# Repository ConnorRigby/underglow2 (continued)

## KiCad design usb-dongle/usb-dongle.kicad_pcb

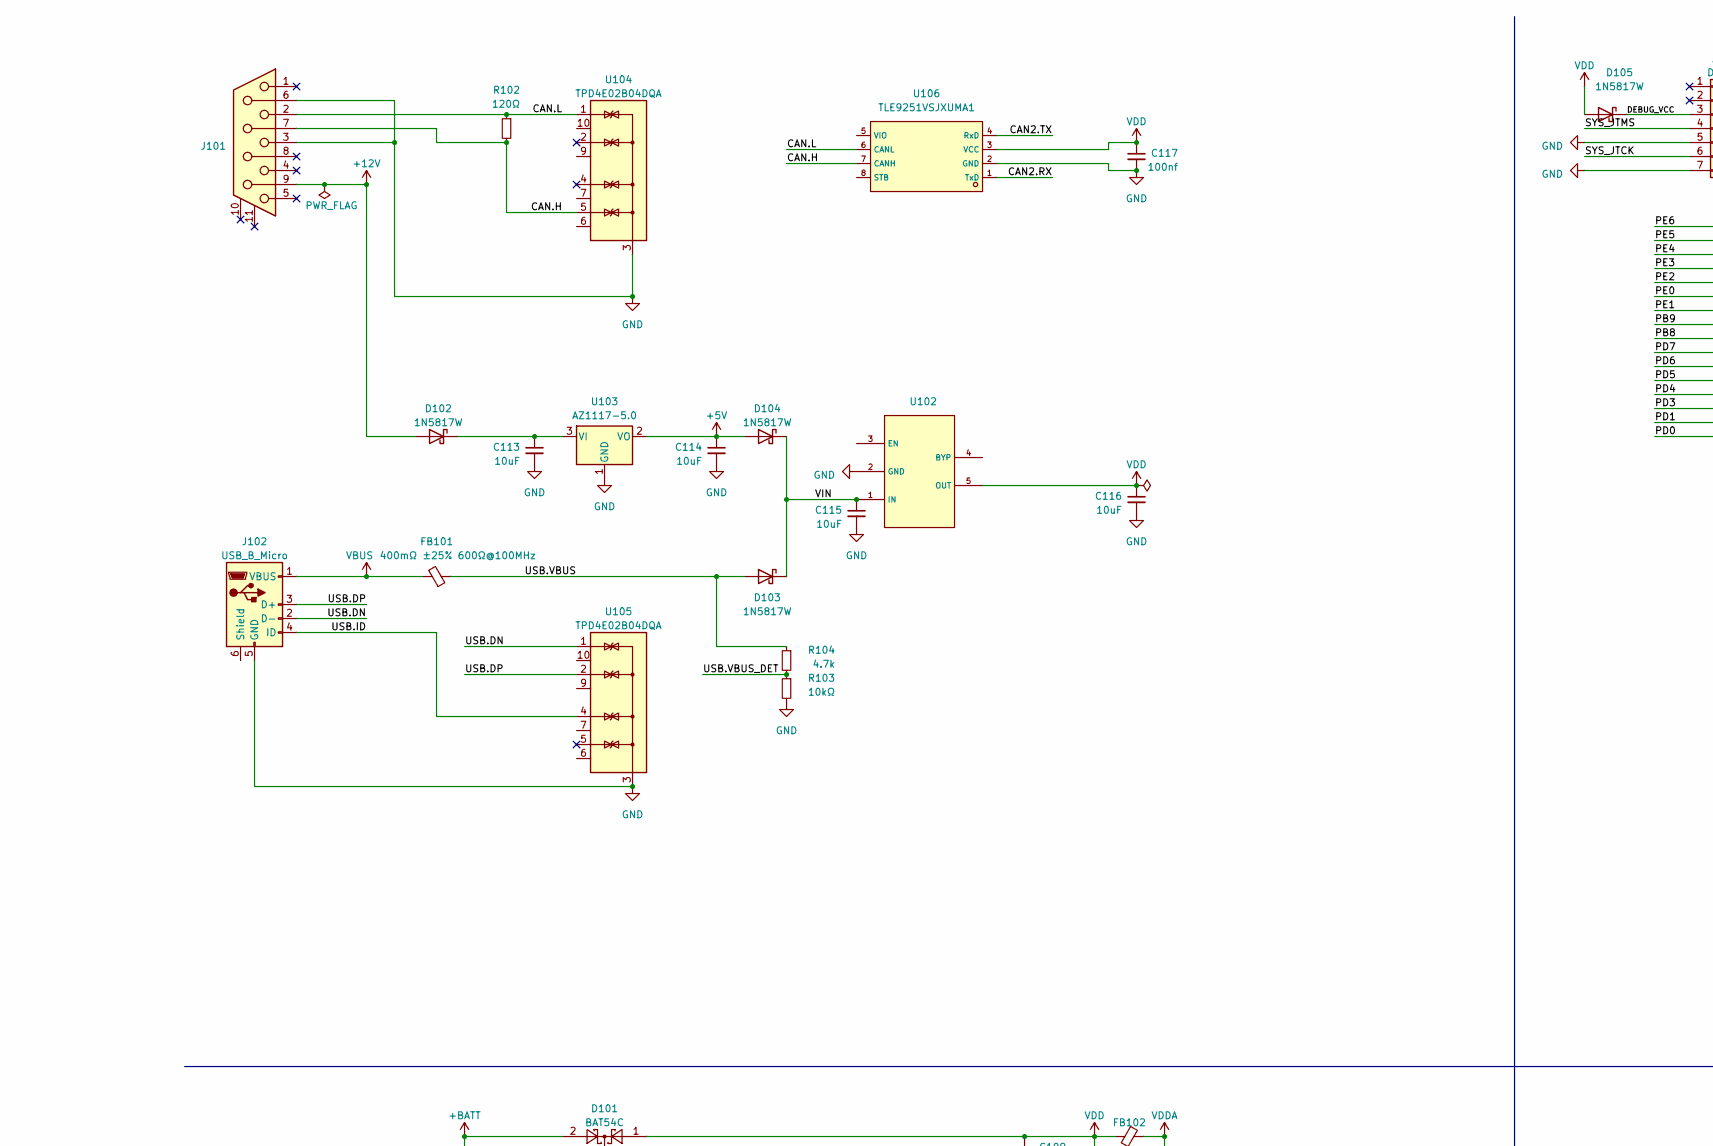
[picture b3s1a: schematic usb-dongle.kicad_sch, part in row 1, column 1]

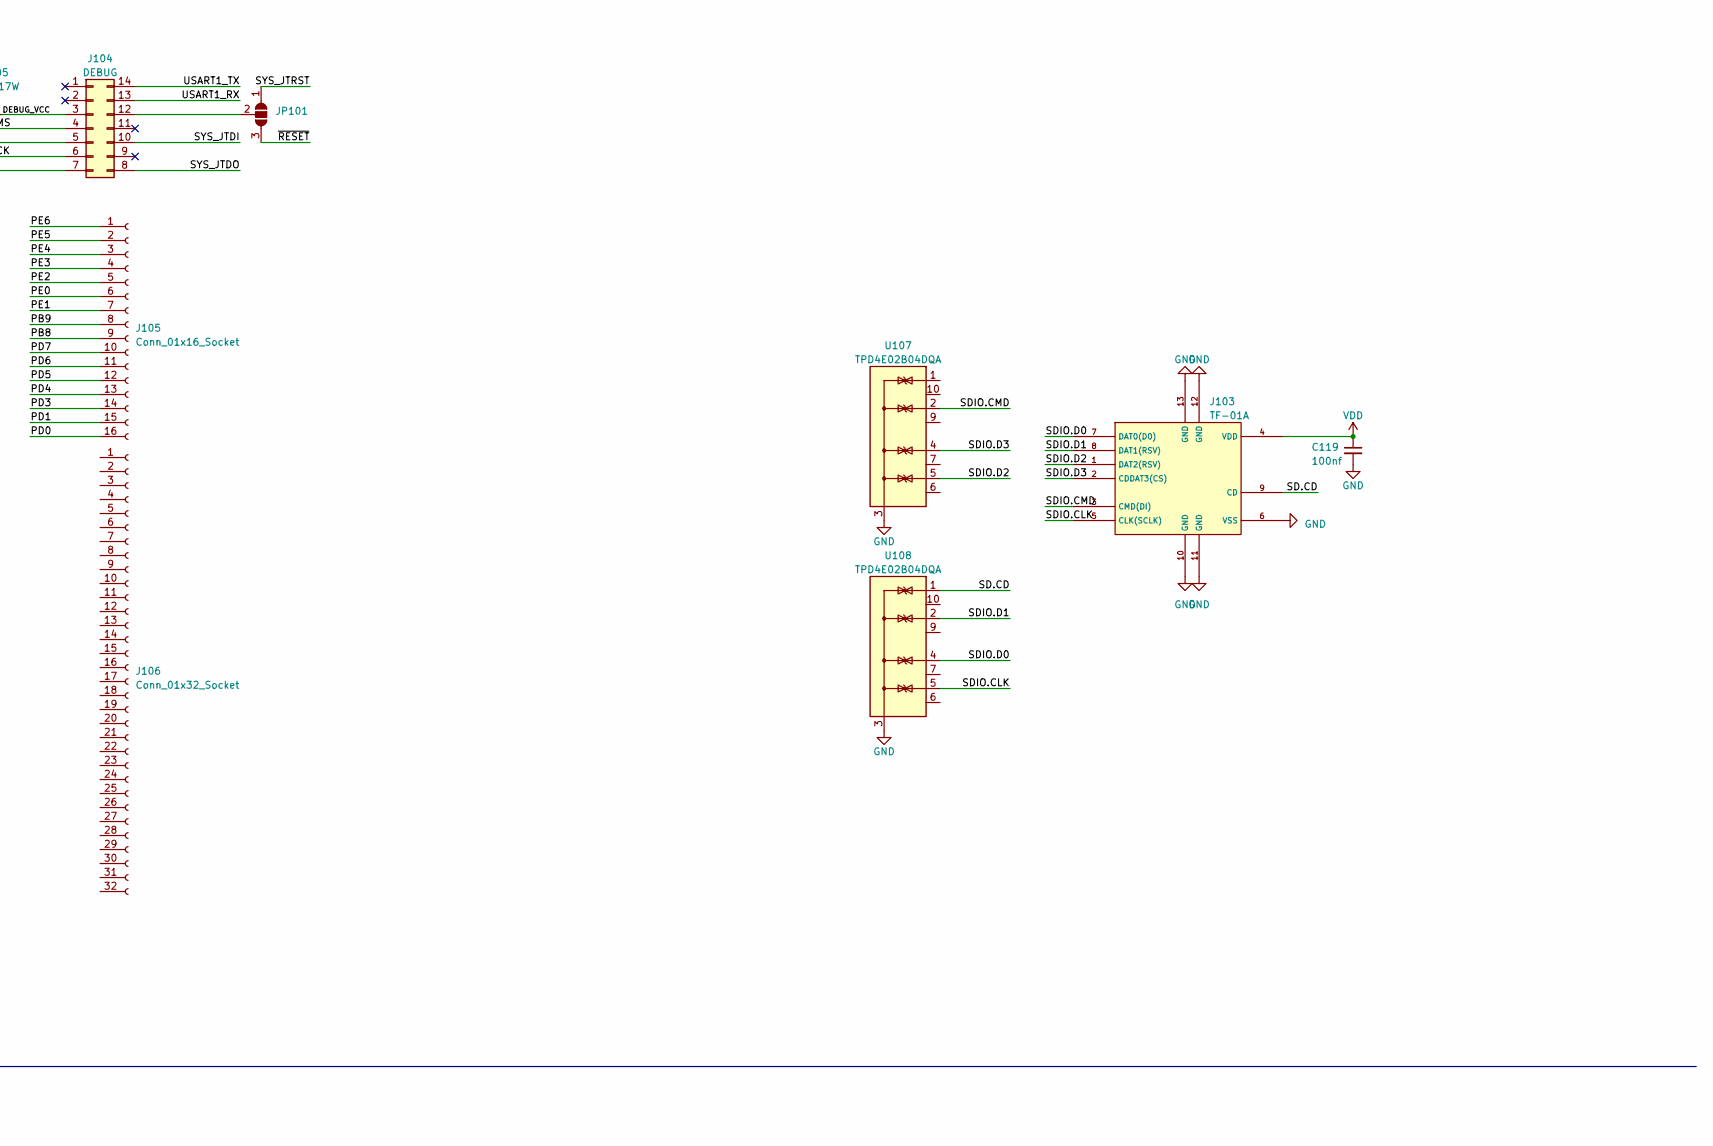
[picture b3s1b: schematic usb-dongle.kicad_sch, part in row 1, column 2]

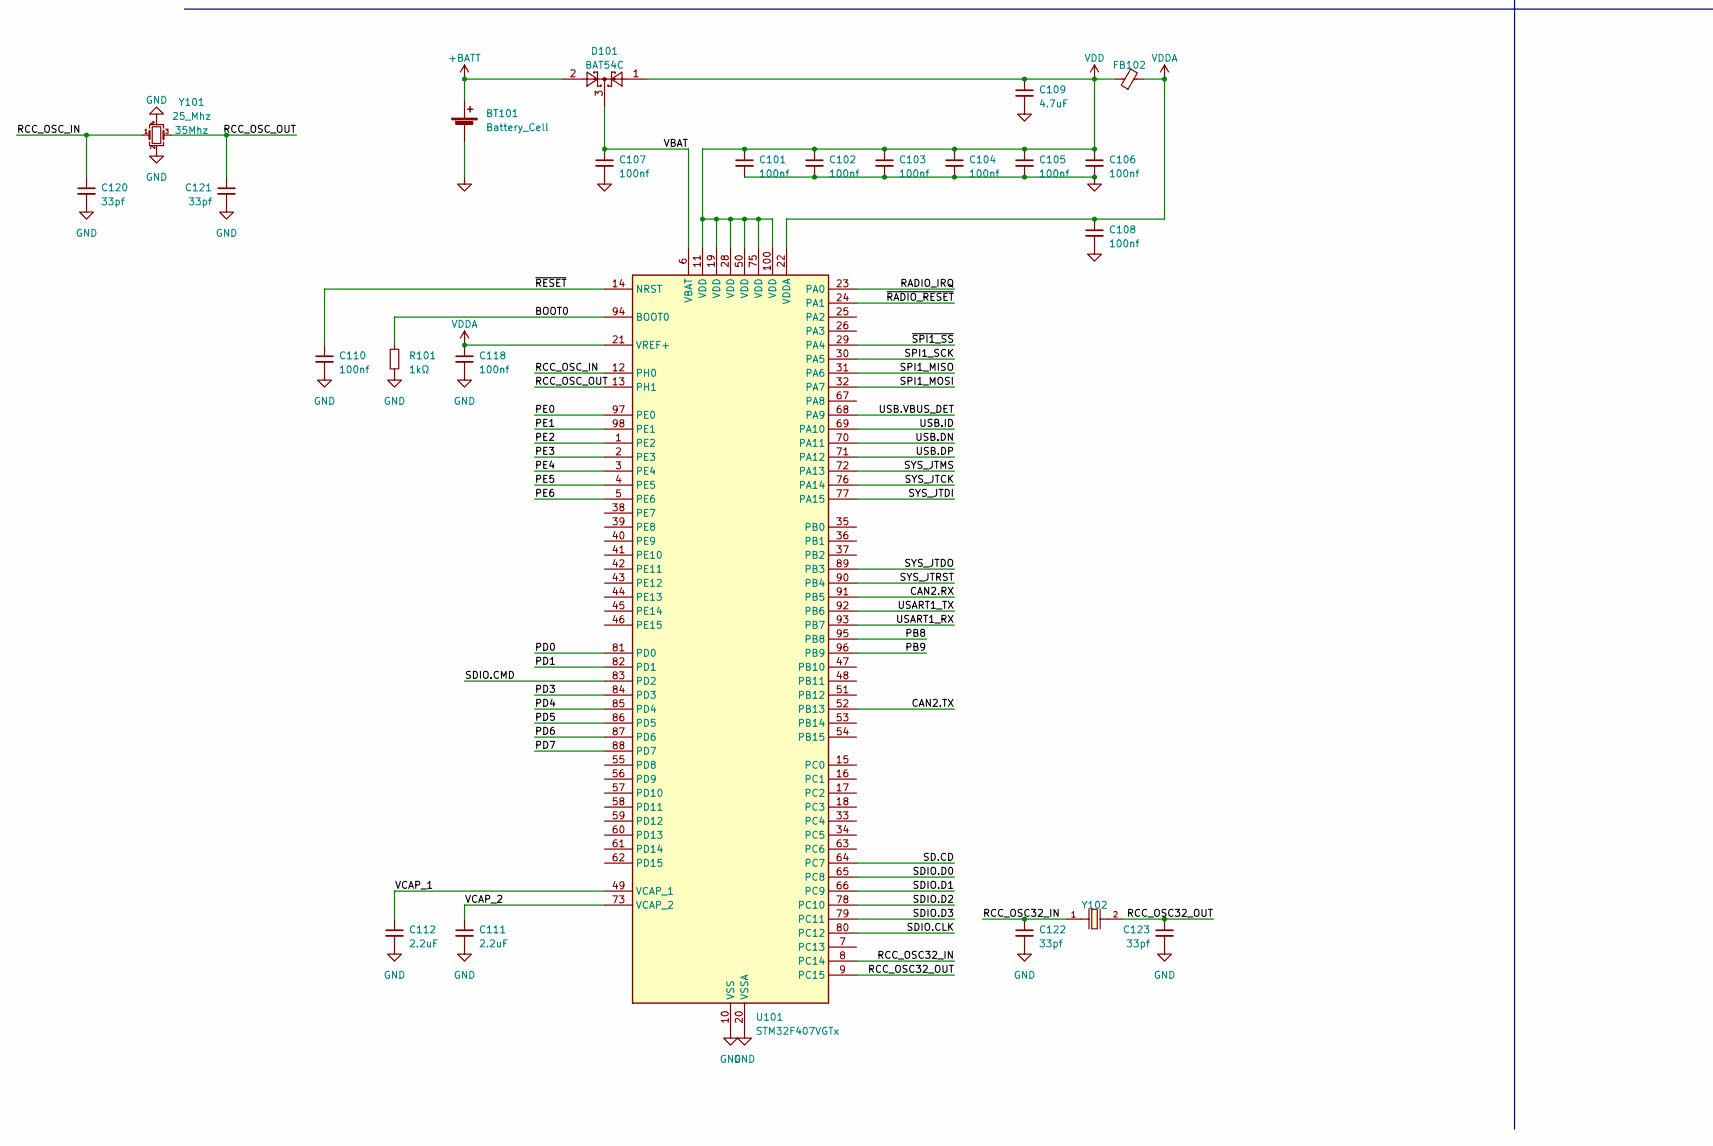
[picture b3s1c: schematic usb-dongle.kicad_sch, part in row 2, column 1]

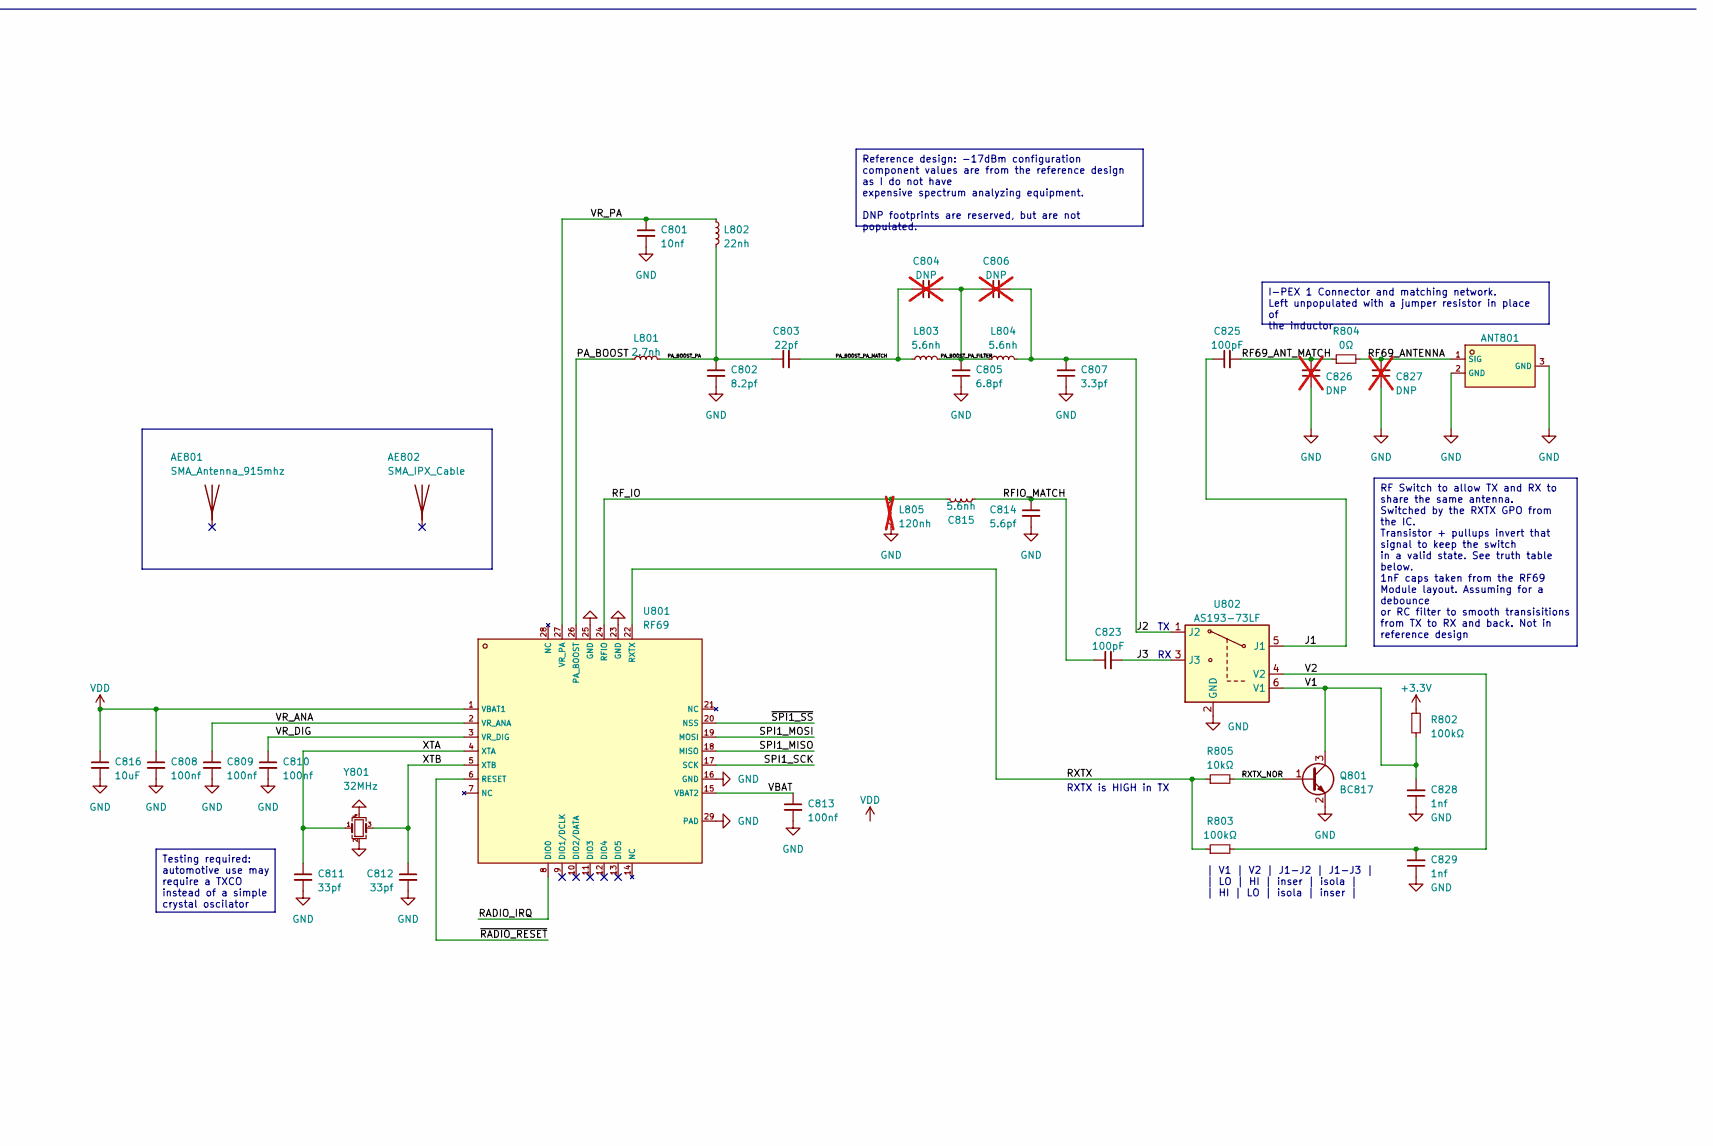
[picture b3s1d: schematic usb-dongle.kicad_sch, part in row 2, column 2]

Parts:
AE801: SMA_Antenna_915mhz; SMA_Antenna_Vertical; MPN TX915-JK-11; LCSC C468327
AE802: SMA_IPX_Cable; SMA_Connector; MPN BWIPX1-SMA-1.13L100; LCSC C784403
ANT801: BWIPX-1-001E; IPEX-SMD_BWIPX-1-001E; MPN BWIPX-1-001E; LCSC C496552
BT101: Battery_Cell; BAT-TH_CR2032-BS-6-1
C101, C102, C103, C104, C105, C106, C107, C108, C110, C117, C118, C119, C808, C809, C810, C813: C_0402_100nf_X7R; C_0402_1005Metric; Voltage 50V; MPN 0402B104K500NT; LCSC C110251
C109: C_0805_4u7_X5R; C_0805_2012Metric; Voltage 6.3; Tolerance 20%; MPN CC0805MKX5R5BB475; LCSC C577033
C111, C112: C_0402_2u2_X75R; C_0402_1005Metric; Voltage 25V; Tolerance 10%; MPN GRM155R61E225KE11D; LCSC C385032
C113, C114, C115, C116, C816: C_0805_10u_X5R; C_0805_2012Metric; Voltage 35V; Tolerance 10%; MPN GRM21BR6YA106KE43L; LCSC C162422
C120, C121, C122, C123, C811, C812: C_0402_33p_C0G; C_0402_1005Metric; Voltage 50V; Tolerance 2%; LCSC C76905
C801: C_0402_10n_C0G; C_0402_1005Metric; Voltage 35V; Tolerance ±5%; MPN GRM1555CYA103JE01D; LCSC C1518210
C802: C_0402_8p2_C0G; C_0402_1005Metric; Voltage 50V; Tolerance 2%; MPN GJM1555C1H8R2CB01D; LCSC C88898
C803: C_0402_22p_C0G; C_0402_1005Metric; Voltage 50V; Tolerance 2%; MPN GJM1555C1H220GB01D; LCSC C161315
C804, C806, C826, C827: C_0402_DNP; C_0402_1005Metric; not fitted
C805: C_0402_6p8_C0G; C_0402_1005Metric; Voltage 50V; Tolerance 2%; MPN GCM1555C1H6R8BA16D; LCSC C354360
C807: C_0402_3p3_C0G; C_0402_1005Metric; Voltage 50V; Tolerance 2%; MPN GRM1555C1H3R3CA01D; LCSC C76968
C814: C_0402_5p6_C0G; C_0402_1005Metric; Voltage 50V; Tolerance 2%; MPN GJM1555C1H5R6CB01D; LCSC C88895
C815: L_0402_5n6; L_0402_1005Metric; MPN LQW15AN5N6C10D; LCSC C91626
C823, C825: C_0402_100p_C0G; C_0402_1005Metric; Voltage 50V; Tolerance 5%; MPN GRT1555C1H101JA02D; LCSC C711072
C828, C829: C_0402_1nf_X7R; C_0402_1005Metric; Voltage 100V; MPN GCM155R72A102KA37D; LCSC C126538
D101: BAT54C; SOT-23
D102, D103, D104, D105: 1N5817W; D_SOD-123; LCSC C727113
FB101: 400mΩ ±25% 600Ω@100MHz; L_0603_1608Metric; LCSC C136491
FB102: FerriteBead_Small; L_0402_1005Metric; LCSC C102745
J101: DE9_Receptacle_MountingHoles; DSUB-TH_DMR-9S; LCSC C141882
J102: USB_B_Micro; MICRO-USB-SMD_MICRO-USB-13; LCSC C91144
J103: TF-01A; TF-SMD_TF-01A; LCSC C91145
J104: DEBUG; TC2070-IDC-FP
J105: Conn_01x16_Socket; PinHeader_1x16_P2.54mm_Vertical
J106: Conn_01x32_Socket; PinSocket_1x32_P2.54mm_Vertical
JP101: SolderJumper_3_Open; SolderJumper-3_P1.3mm_Open_RoundedPad1.0x1.5mm
L801: L_0402_2n7; L_0402_1005Metric; MPN LQW15AN2N7C00D; LCSC C98058
L802: L_0402_22n; L_0402_1005Metric; MPN LQW15AN22NG00D; LCSC C86129
L803, L804: L_0402_5n6; L_0402_1005Metric; MPN LQW15AN5N6C10D; LCSC C91626
L805: L_0402_120n; L_0402_1005Metric; MPN LQW15ANR12J00D; LCSC C113123; not fitted
Q801: BC817; SOT-23; LCSC C39828
R101: R_0402_1k; R_0402_1005Metric; MPN PTFR0402B1K00P9; LCSC C478866
R102: R_1206_120; R_1206_3216Metric; MPN ARG06FTC1200; LCSC C294122
R103, R805: R_0402_10k; R_0402_1005Metric; MPN ARG02BTC1002; LCSC C2902636
R104: 4.7k; R_0402_1005Metric
R802, R803: R_0402_100k; R_0402_1005Metric; MPN ARG02BTC1003; LCSC C2984406
R804: R_0402_0; R_0402_1005Metric; MPN RTT020000FTH; LCSC C102745
U101: STM32F407VGTx; LQFP-100_14x14mm_P0.5mm; LCSC C12345
U102: SPX3819M5-L-3-3_TR; SOT-23-5; LCSC C9055
U103: AZ1117-5.0; SOT-223-3_TabPin2; LCSC C99342
U104, U105, U107, U108: TPD4E02B04DQA; USON-10_2.5x1.0mm_P0.5mm
U106: TLE9251VSJXUMA1; SOIC-8_3.9x4.9mm_P1.27mm; MPN TLE9251VSJ; LCSC C189937
U801: RF69; QFN-28-1EP_5x5mm_P0.5mm_EP3.75x3.75mm_ThermalVias; MPN RF69; LCSC C77220
U802: AS193-73LF; SOT-23-6; MPN AS193-73LF; LCSC C6199
Y101: 25_Mhz; Crystal_SMD_3225-4Pin_3.2x2.5mm; MPN X322525MOB4SI; LCSC C9006
Y102: Q13FC1350000400; Crystal_SMD_3215-2Pin_3.2x1.5mm; LCSC C32346
Y801: 32_Mhz; Crystal_SMD_3225-4Pin_3.2x2.5mm; MPN TAXM32M4RLBCDT2T; LCSC C5143379

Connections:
+3.3V: R802.1
+5V: C114.1, D104.2 (A), U103.2 (VO)
+12V: D102.2 (A), J101.9
+BATT: BT101.1 (+), D101.2
/BOOT0: R101.1, U101.94 (BOOT0)
/CAN2.RX: U101.91 (PB5), U106.1 (TxD)
/CAN2.TX: U101.52 (PB13), U106.4 (RxD)
/CAN.H: J101.7, R102.2, U104.5 (IO4), U106.7 (CANH)
/CAN.L: J101.2, R102.1, U104.1 (IO1), U106.6 (CANL)
/DEBUG_VCC: D105.1 (K), J104.3
/J1: C825.1, U802.5 (J1)
/J2: C806.2, C807.2, L804.2, U802.1 (J2)
/J3: C823.2, U802.3 (J3)
/PA_BOOST: L801.1, U801.26 (PA_BOOST)
/PA_BOOST_PA: C802.1, C803.1, L801.2, L802.2
/PA_BOOST_PA_FILTER: C804.2, C805.2, C806.1, L803.2, L804.1
/PA_BOOST_PA_MATCH: C803.2, C804.1, L803.1
/PB8: J105.9, U101.95 (PB8)
/PB9: J105.8, U101.96 (PB9)
/PD0: J105.16, U101.81 (PD0)
/PD1: J105.15, U101.82 (PD1)
/PD3: J105.14, U101.84 (PD3)
/PD4: J105.13, U101.85 (PD4)
/PD5: J105.12, U101.86 (PD5)
/PD6: J105.11, U101.87 (PD6)
/PD7: J105.10, U101.88 (PD7)
/PE0: J105.6, U101.97 (PE0)
/PE1: J105.7, U101.98 (PE1)
/PE2: J105.5, U101.1 (PE2)
/PE3: J105.4, U101.2 (PE3)
/PE4: J105.3, U101.3 (PE4)
/PE5: J105.2, U101.4 (PE5)
/PE6: J105.1, U101.5 (PE6)
/RADIO_IRQ: U101.23 (PA0), U801.8 (DIO0)
/RCC_OSC32_IN: C122.1, U101.8 (PC14), Y102.1
/RCC_OSC32_OUT: C123.1, U101.9 (PC15), Y102.2
/RCC_OSC_IN: C120.1, U101.12 (PH0), Y101.1
/RCC_OSC_OUT: C121.1, U101.13 (PH1), Y101.3
/RF69_ANTENNA: ANT801.1 (SIG), C827.2, R804.2
/RF69_ANT_MATCH: C825.2, C826.2, R804.1
/RFIO_MATCH: C814.1, C815.1, C823.1
/RF_IO: C815.2, L805.2, U801.24 (RFIO)
/RXTX: R803.1, R805.1, U801.22 (RXTX)
/RXTX_NOR: Q801.1 (B), R805.2
/SD.CD: J103.9 (CD), U101.64 (PC7), U108.1 (IO1)
/SDIO.CLK: J103.5 (CLK(SCLK)), U101.80 (PC12), U108.5 (IO4)
/SDIO.CMD: J103.3 (CMD(DI)), U101.83 (PD2), U107.2 (IO2)
/SDIO.D0: J103.7 (DAT0(D0)), U101.65 (PC8), U108.4 (IO3)
/SDIO.D1: J103.8 (DAT1(RSV)), U101.66 (PC9), U108.2 (IO2)
/SDIO.D2: J103.1 (DAT2(RSV)), U101.78 (PC10), U107.5 (IO4)
/SDIO.D3: J103.2 (CDDAT3(CS)), U101.79 (PC11), U107.4 (IO3)
/SPI1_MISO: U101.31 (PA6), U801.18 (MISO)
/SPI1_MOSI: U101.32 (PA7), U801.19 (MOSI)
/SPI1_SCK: U101.30 (PA5), U801.17 (SCK)
/SYS_JTCK: J104.6, U101.76 (PA14)
/SYS_JTDI: J104.10, U101.77 (PA15)
/SYS_JTDO: J104.8, U101.89 (PB3)
/SYS_JTMS: J104.4, U101.72 (PA13)
/SYS_JTRST: JP101.1 (A), U101.90 (PB4)
/USART1_RX: J104.13, U101.93 (PB7)
/USART1_TX: J104.14, U101.92 (PB6)
/USB.DN: J102.2 (D-), U101.70 (PA11), U105.1 (IO1)
/USB.DP: J102.3 (D+), U101.71 (PA12), U105.2 (IO2)
/USB.ID: J102.4 (ID), U101.69 (PA10), U105.4 (IO3)
/USB.VBUS: D103.2 (A), FB101.1, R104.1
/USB.VBUS_DET: R103.1, R104.2, U101.68 (PA9)
/V1: C828.2, Q801.3 (C), R802.2, U802.6 (V1)
/V2: C829.2, R803.2, U802.4 (V2)
/VBAT: C107.1, C813.1, D101.3, U101.6 (VBAT), U801.15 (VBAT2)
/VCAP_1: C112.1, U101.49 (VCAP_1)
/VCAP_2: C111.1, U101.73 (VCAP_2)
/VIN: C115.1, D103.1 (K), D104.1 (K), U102.1 (IN)
/VR_ANA: C809.1, U801.2 (VR_ANA)
/VR_DIG: C810.1, U801.3 (VR_DIG)
/VR_PA: C801.1, L802.1, U801.27 (VR_PA)
/XTA: C811.1, U801.4 (XTA), Y801.1
/XTB: C812.1, U801.5 (XTB), Y801.3
/~RADIO_RESET: U101.24 (PA1), U801.6 (RESET)
/~RESET: C110.1, JP101.3 (B), U101.14 (NRST)
/~SPI1_SS: U101.29 (PA4), U801.20 (NSS)
GND: ANT801.2 (GND), ANT801.3 (GND), BT101.2 (-), C101.2, C102.2, C103.2, C104.2, C105.2, C106.2, C107.2, C108.2, C109.2, C110.2, C111.2, C112.2, C113.2, C114.2, C115.2, C116.2, C117.2, C118.2, C119.2, C120.2, C121.2, C122.2, C123.2, C801.2, C802.2, C805.1, C807.1, C808.2, C809.2, C810.2, C811.2, C812.2, C813.2, C814.2, C816.2, C826.1, C827.1, C828.1, C829.1, J101.3, J101.6, J102.5 (GND), J103.6 (VSS), J103.10 (GND), J103.11 (GND), J103.12 (GND), J103.13 (GND), J104.5, J104.7, L805.1, Q801.2 (E), R101.2, R103.2, U101.10 (VSS), U101.20 (VSSA), U101.27 (VSS), U101.74 (VSS), U101.99 (VSS), U102.2 (GND), U103.1 (GND), U104.3 (G), U104.8 (G), U105.3 (G), U105.8 (G), U106.2 (GND), U107.3 (G), U107.8 (G), U108.3 (G), U108.8 (G), U801.16 (GND), U801.23 (GND), U801.25 (GND), U801.29 (PAD), U802.2 (GND), Y101.2, Y101.4, Y801.2, Y801.4
unnamed: C113.1, D102.1 (K), U103.3 (VI)
unnamed: J104.12, JP101.2 (C)
VBUS: FB101.2, J102.1 (VBUS)
VDD: C101.1, C102.1, C103.1, C104.1, C105.1, C106.1, C109.1, C116.1, C117.1, C119.1, C808.1, C816.1, D101.1, D105.2 (A), FB102.1, J103.4 (VDD), U101.11 (VDD), U101.19 (VDD), U101.28 (VDD), U101.50 (VDD), U101.75 (VDD), U101.100 (VDD), U102.5 (OUT), U106.3 (VCC), U801.1 (VBAT1)
VDDA: C108.1, C118.1, FB102.2, U101.21 (VREF+), U101.22 (VDDA)

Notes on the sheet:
Testing required: automotive use may require a TXCO instead of a simple crystal oscilator
RF Switch to allow TX and RX to share the same antenna. Switched by the RXTX GPO from the IC. Transistor + pullups invert that signal to keep the switch in a valid state. See truth table below. 1nF caps taken from the RF69 Module layout. Assuming for a debounce or RC filter to smooth transisitions 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
I-PEX 1 Connector and matching network. Left unpopulated with a jumper resistor in place of the inductor.
Reference design: -17dBm configuration component values are from the reference design as I do not have expensive spectrum analyzing equipment. DNP footprints are reserved, but are not populated.
RXTX is HIGH in TX
| V1 | V2 | J1-J2 | J1-J3 | | LO | HI | inser | isola | | HI | LO | isola | inser |

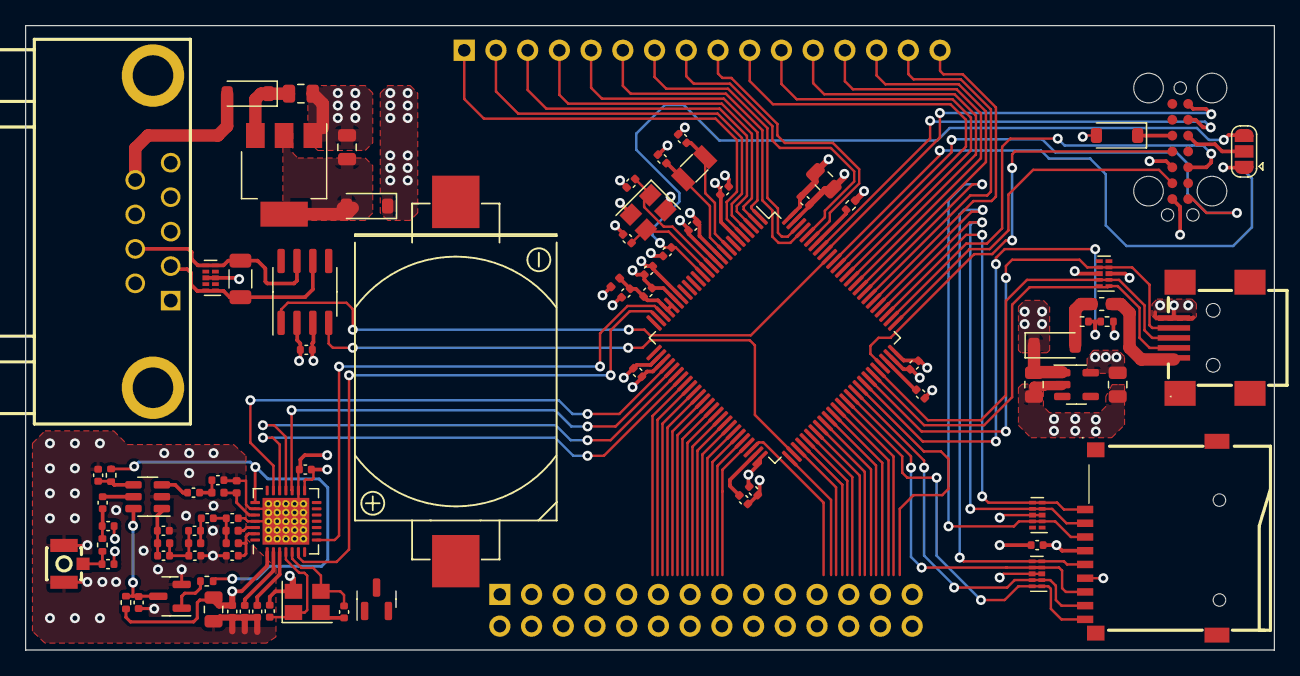
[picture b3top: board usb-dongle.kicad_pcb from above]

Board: 4 copper layers, 100.0 x 50.0 mm, 87 parts (1 on the bottom side), 85 nets.

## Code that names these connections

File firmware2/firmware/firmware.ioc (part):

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PA6.Mode=Full_Duplex_Master
PC7.GPIOParameters=GPIO_Label
PH0-OSC_IN.Signal=RCC_OSC_IN
PE11.GPIOParameters=GPIO_Label
Mcu.UserName=STM32F407VGTx
PC2.Stacked=true
PE11.GPIO_Label=CH1_G
PC10.Signal=SPI3_SCK
PC12.Signal=SPI3_MOSI
PD3.GPIOParameters=GPIO_Label
PC0.GPIOParameters=GPIO_Label
PC0.GPIO_Label=PI1
PC6.GPIO_Label=CH2_NZR
PA3.GPIOParameters=GPIO_Label
PB13.Signal=CAN2_TX
PD6.GPIO_Label=HCI_RX
PA2.GPIOParameters=GPIO_Label
PA4.Mode=NSS_Signal_Hard_Output
PC1.GPIOParameters=GPIO_Label
PD4.Signal=USART2_RTS
PC7.Signal=S_TIM3_CH2
PC3.Signal=SharedStack_PC3
PH0-OSC_IN.Mode=HSE-External-Oscillator
PD5.Mode=Asynchronous
PA0-WKUP.GPIOParameters=GPIO_Label
RCC.HSE_VALUE=8000000
PB3.Mode=JTAG_5_pins
PC13-ANTI_TAMP.Signal=GPXTI13
PA15.Mode=JTAG_5_pins
PA1.GPIOParameters=GPIO_Label
PB4.Mode=JTAG_5_pins
PE13.Signal=S_TIM1_CH3
PC14-OSC32_IN.Mode=LSE-External-Oscillator
PE9.Signal=S_TIM1_CH1
PA14.Mode=JTAG_5_pins
PB5.Mode=CAN_Activate
PA8.Signal=RCC_MCO_1
PD3.Mode=CTS_RTS
PC0.Stacked=true
PH1-OSC_OUT.Mode=HSE-External-Oscillator
Mcu.Package=LQFP100
PA6.Signal=SPI1_MISO
PD5.GPIO_Label=HCI_TX
PD5.GPIOParameters=GPIO_Label
PA2.GPIO_Label=CH2_B
PA10.Signal=USART1_RX
PA15.Signal=SYS_JTDI
PC11.Mode=Full_Duplex_Master
PD4.Mode=CTS_RTS
PD3.GPIO_Label=HCI_CTS
PB13.Mode=CAN_Activate
PD6.Signal=USART2_RX
PC2.GPIO_Label=PI3
PB4.Signal=SYS_JTRST
PA3.Signal=S_TIM2_CH4
PA5.Mode=Full_Duplex_Master
PC13-ANTI_TAMP.GPIOParameters=GPIO_Label
PC15-OSC32_OUT.Mode=LSE-External-Oscillator
PD6.GPIOParameters=GPIO_Label
PA7.Mode=Full_Duplex_Master
PE14.GPIOParameters=GPIO_Label
PA10.Mode=Asynchronous
PC13-ANTI_TAMP.GPIO_Label=RADIO_IRQ
PC11.Signal=SPI3_MISO
PD3.Signal=USART2_CTS
PC8.Signal=S_TIM3_CH3
PC2.Signal=SharedStack_PC2
PC6.Signal=S_TIM3_CH1
PC10.Mode=Full_Duplex_Master
PE14.GPIO_Label=CH1_EN
PD5.Signal=USART2_TX
PC0.Signal=SharedStack_PC0
PC14-OSC32_IN.Signal=RCC_OSC32_IN
PD6.Mode=Asynchronous
PA0-WKUP.GPIO_Label=CH2_R
PA0-WKUP.Signal=S_TIM2_CH1_ETR
PE9.GPIOParameters=GPIO_Label
PC3.GPIOParameters=GPIO_Label
PA13.Signal=SYS_JTMS-SWDIO
PA9.Mode=Asynchronous
PC3.Stacked=true
PA9.Signal=USART1_TX
PE11.Signal=S_TIM1_CH2
PC15-OSC32_OUT.Signal=RCC_OSC32_OUT
PE9.GPIO_Label=CH1_R
PA1.Signal=S_TIM2_CH2
PA5.Signal=SPI1_SCK
PE13.GPIOParameters=GPIO_Label
PC12.Mode=Full_Duplex_Master
board=custom
PE14.Signal=S_TIM1_CH4
PD4.GPIO_Label=HCI_RTS
PC2.GPIOParameters=GPIO_Label
PC1.GPIO_Label=PI2
PA1.GPIO_Label=CH2_G
PD4.GPIOParameters=GPIO_Label
PH1-OSC_OUT.Signal=RCC_OSC_OUT
PA13.Mode=JTAG_5_pins
Mcu.Name=STM32F407V(E-G)Tx
PA2.Signal=S_TIM2_CH3
PC7.GPIO_Label=CH1_NZR
PB3.Signal=SYS_JTDO-SWO
PA4.Signal=SPI1_NSS
RCC.SYSCLKFreq_VALUE=16000000
PB5.Signal=CAN2_RX
PE13.GPIO_Label=CH1_B
PA14.Signal=SYS_JTCK-SWCLK
PC6.GPIOParameters=GPIO_Label
PC3.GPIO_Label=PI4
PA8.Mode=Clock-out-1
PC9.Signal=S_TIM3_CH4
PC1.Stacked=true
PC1.Signal=SharedStack_PC1
PA3.GPIO_Label=CH2_EN
PA7.Signal=SPI1_MOSI

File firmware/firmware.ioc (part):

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Mcu.Name=STM32G431C(6-8-B)Ux
Mcu.Package=UFQFPN48
Mcu.UserName=STM32G431CBUx
PA0.GPIOParameters=GPIO_Label
PA0.GPIO_Label=PI1
PA0.Signal=GPIO_Input
PA1.GPIOParameters=GPIO_Label
PA1.GPIO_Label=PI2
PA1.Signal=GPIO_Input
PA10.GPIOParameters=GPIO_Label
PA10.GPIO_Label=VCP_RX
PA10.Mode=Asynchronous
PA10.Signal=USART1_RX
PA11.GPIOParameters=GPIO_Label
PA11.GPIO_Label=RX_LED
PA11.Signal=GPIO_Output
PA12.GPIOParameters=GPIO_Label
PA12.GPIO_Label=TX_LED
PA12.Signal=GPIO_Output
PA13.Mode=JTAG_5_pins
PA13.Signal=SYS_JTMS-SWDIO
PA14.Mode=JTAG_5_pins
PA14.Signal=SYS_JTCK-SWCLK
PA15.Mode=JTAG_5_pins
PA15.Signal=SYS_JTDI
PA2.GPIOParameters=GPIO_Label
PA2.GPIO_Label=PI3
PA2.Signal=GPIO_Input
PA3.GPIOParameters=GPIO_Label
PA3.GPIO_Label=PI4
PA3.Signal=GPIO_Input
PA4.GPIOParameters=GPIO_Label
PA4.GPIO_Label=R_PWM
PA4.Signal=S_TIM3_CH2
PA6.GPIOParameters=GPIO_Label
PA6.GPIO_Label=G_PWM
PA6.Signal=S_TIM3_CH1
PA7.Mode=Follower_Internally_Connected
PA7.Signal=OPAMP2_VINP
PA9.GPIOParameters=GPIO_Label
PA9.GPIO_Label=VCP_TX
PA9.Mode=Asynchronous
PA9.Signal=USART1_TX
PB0.Mode=Follower_Internally_Connected
PB0.Signal=OPAMP3_VINP
PB1.GPIOParameters=GPIO_Label
PB1.GPIO_Label=B_PWM
PB1.Signal=S_TIM3_CH4
PB10.GPIOParameters=GPIO_Label
PB10.GPIO_Label=BLE_RX
PB10.Mode=Asynchronous
PB10.Signal=LPUART1_RX
PB11.GPIOParameters=GPIO_Label
PB11.GPIO_Label=BLE_TX
PB11.Mode=Asynchronous
PB11.Signal=LPUART1_TX
PB12.GPIOParameters=GPIO_Label
PB12.GPIO_Label=BLE_RTS
PB12.Mode=CTS_RTS
PB12.Signal=LPUART1_RTS
PB13.GPIOParameters=GPIO_Label
PB13.GPIO_Label=BLE_CTS
PB13.Mode=CTS_RTS
PB13.Signal=LPUART1_CTS
PB3.Mode=JTAG_5_pins
PB3.Signal=SYS_JTDO-SWO
PB4.Mode=JTAG_5_pins
PB4.Signal=SYS_JTRST
PB6.GPIOParameters=GPIO_Label
PB6.GPIO_Label=NZR2
PB6.Signal=S_TIM4_CH1
PB7.GPIOParameters=GPIO_Label
PB7.GPIO_Label=NZR1
PB7.Signal=S_TIM4_CH2
PB8-BOOT0.Mode=FDCAN_Activate
PB8-BOOT0.Signal=FDCAN1_RX
PB9.Mode=FDCAN_Activate
PB9.Signal=FDCAN1_TX
PC14-OSC32_IN.Mode=LSE-External-Oscillator
PC14-OSC32_IN.Signal=RCC_OSC32_IN
PC15-OSC32_OUT.Mode=LSE-External-Oscillator
PC15-OSC32_OUT.Signal=RCC_OSC32_OUT
PF0-OSC_IN.Mode=HSE-External-Oscillator
PF0-OSC_IN.Signal=RCC_OSC_IN
PF1-OSC_OUT.Mode=HSE-External-Oscillator
PF1-OSC_OUT.Signal=RCC_OSC_OUT
PG10-NRST.GPIOParameters=GPIO_Label
PG10-NRST.GPIO_Label=NRESET
PG10-NRST.Signal=GPIO_Output
RCC.HSE_VALUE=32000000
RCC.SYSCLKFreq_VALUE=96000000
RCC.SYSCLKSource=RCC_SYSCLKSOURCE_PLLCLK
board=custom

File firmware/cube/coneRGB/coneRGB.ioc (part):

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Mcu.Name=STM32F407V(E-G)Tx
Mcu.Package=LQFP100
Mcu.UserName=STM32F407VGTx
PA0-WKUP.GPIOParameters=GPIO_Label
PA0-WKUP.GPIO_Label=B1 [Blue PushButton]
PA0-WKUP.Signal=GPXTI0
PA10.GPIOParameters=GPIO_Speed,GPIO_PuPd,GPIO_Label,GPIO_Mode
PA10.GPIO_Label=OTG_FS_ID
PA10.GPIO_Mode=GPIO_MODE_AF_PP
PA10.GPIO_PuPd=GPIO_NOPULL
PA10.GPIO_Speed=GPIO_SPEED_FREQ_LOW
PA10.Signal=USB_OTG_FS_ID
PA11.GPIOParameters=GPIO_Speed,GPIO_PuPd,GPIO_Label,GPIO_Mode
PA11.GPIO_Label=OTG_FS_DM
PA11.GPIO_Mode=GPIO_MODE_AF_PP
PA11.GPIO_PuPd=GPIO_NOPULL
PA11.GPIO_Speed=GPIO_SPEED_FREQ_LOW
PA11.Signal=USB_OTG_FS_DM
PA12.GPIOParameters=GPIO_Speed,GPIO_PuPd,GPIO_Label,GPIO_Mode
PA12.GPIO_Label=OTG_FS_DP
PA12.GPIO_Mode=GPIO_MODE_AF_PP
PA12.GPIO_PuPd=GPIO_NOPULL
PA12.GPIO_Speed=GPIO_SPEED_FREQ_LOW
PA12.Signal=USB_OTG_FS_DP
PA13.GPIOParameters=GPIO_Label
PA13.GPIO_Label=SWDIO
PA13.Mode=Trace_Asynchronous_SW
PA13.Signal=SYS_JTMS-SWDIO
PA14.GPIOParameters=GPIO_Label
PA14.GPIO_Label=SWCLK
PA14.Mode=Trace_Asynchronous_SW
PA14.Signal=SYS_JTCK-SWCLK
PA15.Signal=GPIO_Output
PA2.Mode=Asynchronous
PA2.Signal=USART2_TX
PA3.Mode=Asynchronous
PA3.Signal=USART2_RX
PA4.GPIOParameters=GPIO_Speed,GPIO_PuPd,GPIO_Label,GPIO_Mode
PA4.GPIO_Label=I2S3_WS [CS43L22_LRCK]
PA4.GPIO_Mode=GPIO_MODE_AF_PP
PA4.GPIO_PuPd=GPIO_NOPULL
PA4.GPIO_Speed=GPIO_SPEED_FREQ_LOW
PA4.Signal=I2S3_WS
PA5.GPIOParameters=GPIO_Speed,GPIO_PuPd,GPIO_Label,GPIO_Mode
PA5.GPIO_Label=SPI1_SCK [LIS302DL_SCL/SPC]
PA5.GPIO_Mode=GPIO_MODE_AF_PP
PA5.GPIO_PuPd=GPIO_NOPULL
PA5.GPIO_Speed=GPIO_SPEED_FREQ_LOW
PA5.Mode=Full_Duplex_Master
PA5.Signal=SPI1_SCK
PA6.GPIOParameters=GPIO_Speed,GPIO_PuPd,GPIO_Label,GPIO_Mode
PA6.GPIO_Label=SPI1_MISO [LIS302DL_SDO]
PA6.GPIO_Mode=GPIO_MODE_AF_PP
PA6.GPIO_PuPd=GPIO_NOPULL
PA6.GPIO_Speed=GPIO_SPEED_FREQ_LOW
PA6.Mode=Full_Duplex_Master
PA6.Signal=SPI1_MISO
PA7.GPIOParameters=GPIO_Speed,GPIO_PuPd,GPIO_Label,GPIO_Mode
PA7.GPIO_Label=SPI1_MOSI [LIS302DL_SDA/SDI/SDO]
PA7.GPIO_Mode=GPIO_MODE_AF_PP
PA7.GPIO_PuPd=GPIO_NOPULL
PA7.GPIO_Speed=GPIO_SPEED_FREQ_LOW
PA7.Mode=Full_Duplex_Master
PA7.Signal=SPI1_MOSI
PA9.GPIOParameters=GPIO_PuPd,GPIO_Label,GPIO_Mode
PA9.GPIO_Label=VBUS_FS
PA9.GPIO_Mode=GPIO_MODE_INPUT
PA9.GPIO_PuPd=GPIO_NOPULL
PA9.Signal=USB_OTG_FS_VBUS
PB10.GPIOParameters=GPIO_Speed,GPIO_PuPd,GPIO_Label,GPIO_Mode
PB10.GPIO_Label=CLK_IN [MP45DT02_CLK]
PB10.GPIO_Mode=GPIO_MODE_AF_PP
PB10.GPIO_PuPd=GPIO_NOPULL
PB10.GPIO_Speed=GPIO_SPEED_FREQ_LOW
PB10.Signal=I2S2_CK
PB12.Mode=NSS_Signal_Hard_Output
PB12.Signal=SPI2_NSS
PB13.Mode=Full_Duplex_Master
PB13.Signal=SPI2_SCK
PB14.Mode=Full_Duplex_Master
PB14.Signal=SPI2_MISO
PB15.Mode=Full_Duplex_Master
PB15.Signal=SPI2_MOSI
PB2.Signal=GPIO_Input
PB3.GPIOParameters=GPIO_Label
PB3.GPIO_Label=SWO
PB3.Mode=Trace_Asynchronous_SW
PB3.Signal=SYS_JTDO-SWO
PB5.GPIOParameters=GPIO_PuPd,GPIO_Label
PB5.GPIO_Label=RF69_RESET
PB5.GPIO_PuPd=GPIO_PULLUP
PB5.Signal=GPIO_Output
PB6.GPIOParameters=GPIO_Speed,GPIO_PuPd,GPIO_Label,GPIO_Mode
PB6.GPIO_Label=Audio_SCL [CS43L22_SCL]
PB6.GPIO_Mode=GPIO_MODE_AF_OD
PB6.GPIO_PuPd=GPIO_NOPULL
PB6.GPIO_Speed=GPIO_SPEED_FREQ_LOW
PB6.Signal=I2C1_SCL
PB7.GPIOParameters=GPIO_Label
PB7.GPIO_Label=RF69_IRQ
PB7.Signal=GPIO_Input
PB9.GPIOParameters=GPIO_Speed,GPIO_PuPd,GPIO_Label,GPIO_Mode
PB9.GPIO_Label=Audio_SDA [CS43L22_SDA]
PB9.GPIO_Mode=GPIO_MODE_AF_OD
PB9.GPIO_PuPd=GPIO_NOPULL
PB9.GPIO_Speed=GPIO_SPEED_FREQ_LOW
PB9.Signal=I2C1_SDA
PC0.GPIOParameters=GPIO_Speed,PinState,GPIO_PuPd,GPIO_Label
PC0.GPIO_Label=OTG_FS_PowerSwitchOn
PC0.GPIO_PuPd=GPIO_NOPULL
PC0.GPIO_Speed=GPIO_SPEED_FREQ_LOW
PC0.PinState=GPIO_PIN_SET
PC0.Signal=GPIO_Output
PC10.GPIOParameters=GPIO_Speed,GPIO_PuPd,GPIO_Label,GPIO_Mode
PC10.GPIO_Label=I2S3_SCK [CS43L22_SCLK]
PC10.GPIO_Mode=GPIO_MODE_AF_PP
PC10.GPIO_PuPd=GPIO_NOPULL
PC10.GPIO_Speed=GPIO_SPEED_FREQ_LOW
PC10.Signal=I2S3_CK
PC12.GPIOParameters=GPIO_Speed,GPIO_PuPd,GPIO_Label,GPIO_Mode
PC12.GPIO_Label=I2S3_SD [CS43L22_SDIN]
PC12.GPIO_Mode=GPIO_MODE_AF_PP
PC12.GPIO_PuPd=GPIO_NOPULL
PC12.GPIO_Speed=GPIO_SPEED_FREQ_LOW
PC12.Signal=I2S3_SD
PC14-OSC32_IN.GPIOParameters=GPIO_Label
PC14-OSC32_IN.GPIO_Label=PC14-OSC32_IN
PC14-OSC32_IN.Signal=RCC_OSC32_IN
PC15-OSC32_OUT.GPIOParameters=GPIO_Label
PC15-OSC32_OUT.GPIO_Label=PC15-OSC32_OUT
PC15-OSC32_OUT.Signal=RCC_OSC32_OUT
PC3.GPIOParameters=GPIO_Speed,GPIO_PuPd,GPIO_Label,GPIO_Mode
PC3.GPIO_Label=PDM_OUT [MP45DT02_DOUT]
PC3.GPIO_Mode=GPIO_MODE_AF_PP
PC3.GPIO_PuPd=GPIO_NOPULL
PC3.GPIO_Speed=GPIO_SPEED_FREQ_LOW
PC3.Signal=I2S2_SD
PC7.GPIOParameters=GPIO_Speed,GPIO_PuPd,GPIO_Label,GPIO_Mode
PC7.GPIO_Label=I2S3_MCK [CS43L22_MCLK]
PC7.GPIO_Mode=GPIO_MODE_AF_PP
PC7.GPIO_PuPd=GPIO_NOPULL
PC7.GPIO_Speed=GPIO_SPEED_FREQ_LOW
PC7.Signal=I2S3_MCK
PD12.GPIOParameters=GPIO_Speed,GPIO_PuPd,GPIO_Label
PD12.GPIO_Label=LD4 [Green Led]
PD12.GPIO_PuPd=GPIO_NOPULL
PD12.GPIO_Speed=GPIO_SPEED_FREQ_LOW
PD12.Signal=GPIO_Output
PD13.GPIOParameters=GPIO_Speed,GPIO_PuPd,GPIO_Label
PD13.GPIO_Label=LD3 [Orange Led]
PD13.GPIO_PuPd=GPIO_NOPULL
PD13.GPIO_Speed=GPIO_SPEED_FREQ_LOW
PD13.Signal=GPIO_Output
PD14.GPIOParameters=GPIO_Speed,GPIO_PuPd,GPIO_Label
PD14.GPIO_Label=LD5 [Red Led]
PD14.GPIO_PuPd=GPIO_NOPULL
PD14.GPIO_Speed=GPIO_SPEED_FREQ_LOW
PD14.Signal=GPIO_Output
PD15.GPIOParameters=GPIO_Speed,GPIO_PuPd,GPIO_Label
PD15.GPIO_Label=LD6 [Blue Led]
PD15.GPIO_PuPd=GPIO_NOPULL
PD15.GPIO_Speed=GPIO_SPEED_FREQ_LOW
PD15.Signal=GPIO_Output
PD4.GPIOParameters=GPIO_Speed,GPIO_PuPd,GPIO_Label
PD4.GPIO_Label=Audio_RST [CS43L22_RESET]
PD4.GPIO_PuPd=GPIO_NOPULL
PD4.GPIO_Speed=GPIO_SPEED_FREQ_LOW
PD4.Signal=GPIO_Output
PD5.GPIOParameters=GPIO_PuPd,GPIO_Label,GPIO_Mode
PD5.GPIO_Label=OTG_FS_OverCurrent
PD5.GPIO_Mode=GPIO_MODE_INPUT
PD5.GPIO_PuPd=GPIO_NOPULL
PD5.Signal=GPIO_Input
PE1.GPIOParameters=GPIO_PuPd,GPIO_Label,GPIO_ModeDefaultEXTI
PE1.GPIO_Label=MEMS_INT2 [LIS302DL_INT2]
PE1.GPIO_ModeDefaultEXTI=GPIO_MODE_EVT_RISING
PE1.GPIO_PuPd=GPIO_NOPULL
PE1.Signal=GPXTI1
PE3.Signal=GPIO_Output
PH0-OSC_IN.GPIOParameters=GPIO_Label
PH0-OSC_IN.GPIO_Label=PH0-OSC_IN
PH0-OSC_IN.Mode=HSE-External-Oscillator
PH0-OSC_IN.Signal=RCC_OSC_IN
PH1-OSC_OUT.GPIOParameters=GPIO_Label
PH1-OSC_OUT.GPIO_Label=PH1-OSC_OUT
PH1-OSC_OUT.Mode=HSE-External-Oscillator
PH1-OSC_OUT.Signal=RCC_OSC_OUT
RCC.HSE_VALUE=8000000
RCC.SYSCLKFreq_VALUE=25000000
RCC.SYSCLKSource=RCC_SYSCLKSOURCE_PLLCLK
board=STM32F407G-DISC1
boardIOC=true

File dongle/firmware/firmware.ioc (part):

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Mcu.Name=STM32G431C(6-8-B)Ux
Mcu.Package=UFQFPN48
Mcu.UserName=STM32G431CBUx
PA10.Mode=Asynchronous
PA10.Signal=USART1_RX
PA11.Mode=Device
PA11.Signal=USB_DM
PA12.Mode=Device
PA12.Signal=USB_DP
PA13.Mode=JTAG_5_pins
PA13.Signal=SYS_JTMS-SWDIO
PA14.Mode=JTAG_5_pins
PA14.Signal=SYS_JTCK-SWCLK
PA15.Mode=JTAG_5_pins
PA15.Signal=SYS_JTDI
PA2.GPIOParameters=GPIO_Label
PA2.GPIO_Label=RADIO_RESET
PA2.Signal=GPIO_Output
PA3.GPIOParameters=GPIO_Label
PA3.GPIO_Label=RADIO_IRQ
PA3.Signal=GPXTI3
PA4.GPIOParameters=GPIO_Label
PA4.GPIO_Label=RADIO_NSS
PA4.Signal=GPIO_Output
PA5.GPIOParameters=GPIO_Label
PA5.GPIO_Label=RADIO_SCK
PA5.Mode=Full_Duplex_Master
PA5.Signal=SPI1_SCK
PA6.GPIOParameters=GPIO_Label
PA6.GPIO_Label=RADIO_MISO
PA6.Mode=Full_Duplex_Master
PA6.Signal=SPI1_MISO
PA7.GPIOParameters=GPIO_Label
PA7.GPIO_Label=RADIO_MOSI
PA7.Mode=Full_Duplex_Master
PA7.Signal=SPI1_MOSI
PA9.Mode=Asynchronous
PA9.Signal=USART1_TX
PB12.GPIOParameters=GPIO_Label
PB12.GPIO_Label=SPIFLASH_NSS
PB12.Signal=GPIO_Output
PB13.GPIOParameters=GPIO_Label
PB13.GPIO_Label=SPIFLASH_SCK
PB13.Mode=Full_Duplex_Master
PB13.Signal=SPI2_SCK
PB14.GPIOParameters=GPIO_Label
PB14.GPIO_Label=SPIFLASH_MISO
PB14.Mode=Full_Duplex_Master
PB14.Signal=SPI2_MISO
PB15.GPIOParameters=GPIO_Label
PB15.GPIO_Label=SPIFLASH_MOSI
PB15.Mode=Full_Duplex_Master
PB15.Signal=SPI2_MOSI
PB3.Mode=JTAG_5_pins
PB3.Signal=SYS_JTDO-SWO
PB4.Mode=JTAG_5_pins
PB4.Signal=SYS_JTRST
PB5.GPIOParameters=GPIO_Label
PB5.GPIO_Label=RF_TX
PB5.Signal=GPIO_Output
PB6.GPIOParameters=GPIO_Label
PB6.GPIO_Label=RF_RX
PB6.Signal=GPIO_Output
PB7.GPIOParameters=GPIO_Label
PB7.GPIO_Label=USB_RX
PB7.Signal=GPIO_Input
PB8-BOOT0.GPIOParameters=GPIO_Label
PB8-BOOT0.GPIO_Label=USB_TX
PB8-BOOT0.Signal=GPIO_Output
PF0-OSC_IN.Mode=HSE-External-Oscillator
PF0-OSC_IN.Signal=RCC_OSC_IN
PF1-OSC_OUT.Mode=HSE-External-Oscillator
PF1-OSC_OUT.Signal=RCC_OSC_OUT
RCC.HSE_VALUE=32000000
RCC.SYSCLKFreq_VALUE=16000000
board=custom

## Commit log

2023-03-01 Schematic progress
2023-03-01 Schematic updates: stm32 sheet
2023-03-11 Schematic and layout Progress
2023-03-13 Layout updates
2023-03-13 Update layout
2023-03-20 RF layout updates
2023-03-20 Almost ready for fab
2023-03-21 Pre-production updates
2023-03-21 Add Case and other models
2023-03-21 More pre-production updates:
    * fix USART connections being reversed
    * add test points for SPI and BLE
2023-03-22 Submitted for production
2023-03-22 Update README.md and docs
2023-03-23 Add initial cubemx firmware
2023-03-23 Makefile update
2023-03-24 Add HALs for gpio and SPI
2023-03-25 HAL updates
2023-03-25 CAN HAL driver
2023-03-28 Start adding a nds powered remote control
2023-03-30 board layout testing for nds remote
2023-04-05 Generate firmware for STM32G4
2023-04-06 Btstack updates
2023-04-06 Scafold simple syncing algorithm
2023-04-07 Add stubbed shell application
2023-04-07 Implement gatt services for RGB channels and sync config
2023-04-08 Implement digital input configuration
2023-04-08 digital input updates
2023-04-09 immplement basic run loop structure
2023-04-09 Bootstrap simple UI for testing
2023-04-09 Implement basic fill and snake patterns
2023-04-10 Cap FPS to 30 ish Signed-off-by: Connor Rigby <connorr@hey.com>
2023-04-10 Implement param framework for patterns
2023-04-17 hardware: Add flash storage
2023-04-17 hardware: add USB for debugging and programming
2023-04-26 Initial firmware bringup
2023-04-27 radio bootstrapping
2023-04-27 Radio firmware initialization
2023-04-28 honk
2023-04-28 radio works
2023-04-29 Implement basic neopixel driver
2023-04-29 implement digital input and channel state
2023-04-30 HW updates and folder cleanup
2023-05-02 dongle: wip
2023-05-04 Rev 2 submitted for production
2023-05-09 Bootstrap documentation
2023-05-09 Dongle rev 1
2023-05-29 ughhhhhhhhhhhhhhhhhhhhhhhhhhhhhhhhhhhhhhhhhhhhhhhhhhh
2023-05-29 asdf
2023-06-28 Add 3d render
2023-08-25 Prepare for Production
2023-09-08 submit for production
